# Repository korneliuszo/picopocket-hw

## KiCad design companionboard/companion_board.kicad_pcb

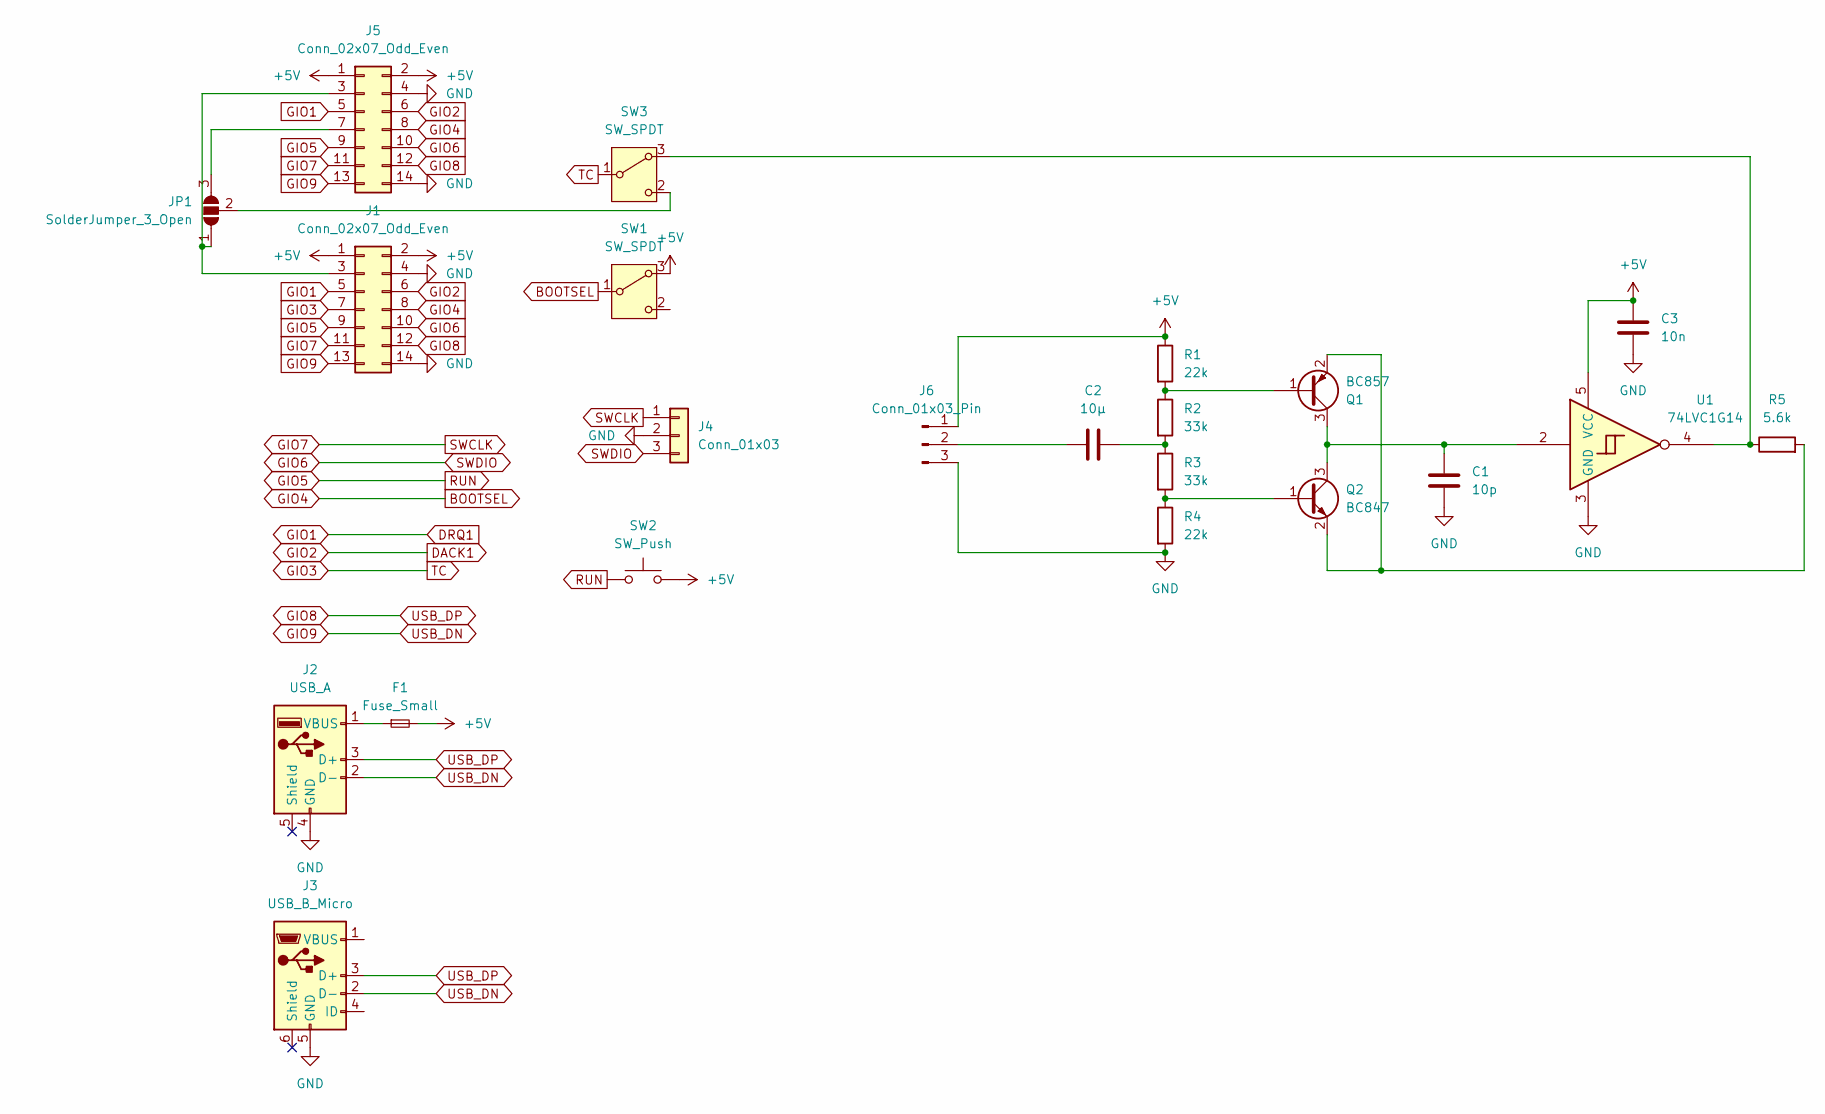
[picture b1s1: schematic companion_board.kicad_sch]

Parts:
C1: 10p; C_0805_2012Metric
C2: 10µ; C_0805_2012Metric
C3: 10n; C_0805_2012Metric
F1: Fuse_Small; Fuse_0805_2012Metric
J1: Conn_02x07_Odd_Even; EDGE-14
J2: USB_A; USB_A_CONNFLY_DS1095-WNR0
J3: USB_B_Micro; USB_Micro-B_Wuerth_614105150721_Vertical
J4: Conn_01x03; PinHeader_1x03_P2.54mm_Vertical
J5: Conn_02x07_Odd_Even; PinSocket_2x07_P2.00mm_Vertical
J6: Conn_01x03_Pin; PinHeader_1x03_P2.54mm_Vertical
JP1: SolderJumper_3_Open; SolderJumper-3_P2.0mm_Open_TrianglePad1.0x1.5mm
Q1: BC857; SOT-23
Q2: BC847; SOT-23
R1, R4: 22k; R_0402_1005Metric_Pad0.72x0.64mm_HandSolder
R2, R3: 33k; R_0402_1005Metric_Pad0.72x0.64mm_HandSolder
R5: 5.6k; R_0402_1005Metric_Pad0.72x0.64mm_HandSolder
SW1, SW3: SW_SPDT; SW_Slide-03_Wuerth-WS-SLTV_10x2.5x6.4_P2.54mm
SW2: SW_Push; SW_PUSH_6mm
U1: 74LVC1G14; SOT-353_SC-70-5_Handsoldering

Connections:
+5V: C3.1, F1.2, J1.1, J1.2, J5.1, J5.2, J6.1, R1.1, SW1.3 (A), SW2.2, U1.5 (VCC)
BOOTSEL: J1.8, J5.8, SW1.1 (B)
DACK1: J1.6, J5.6
DRQ1: J1.5, J5.5
GIO3: J1.7, SW3.1 (B)
GIO5: J1.9, J5.9, SW2.1
GIO6: J1.10, J4.3, J5.10
GIO7: J1.11, J4.1, J5.11
GIO8: J1.12, J2.3 (D+), J3.3 (D+), J5.12
GIO9: J1.13, J2.2 (D-), J3.2 (D-), J5.13
GND: C1.2, C3.2, J1.4, J1.14, J2.4 (GND), J3.5 (GND), J4.2, J5.4, J5.14, J6.3, R4.2, U1.3 (GND)
unnamed: C2.2, R2.2, R3.1
unnamed: J1.3, J5.3, JP1.1 (A)
unnamed: F1.1, J2.1 (VBUS)
unnamed: J5.7, JP1.3 (B)
unnamed: C2.1, J6.2
unnamed: JP1.2 (C), SW3.2 (C)
unnamed: Q1.1 (B), R1.2, R2.1
unnamed: C1.1, Q1.3 (C), Q2.3 (C), U1.2
unnamed: Q1.2 (E), Q2.2 (E), R5.2
unnamed: Q2.1 (B), R3.2, R4.1
unnamed: R5.1, SW3.3 (A), U1.4

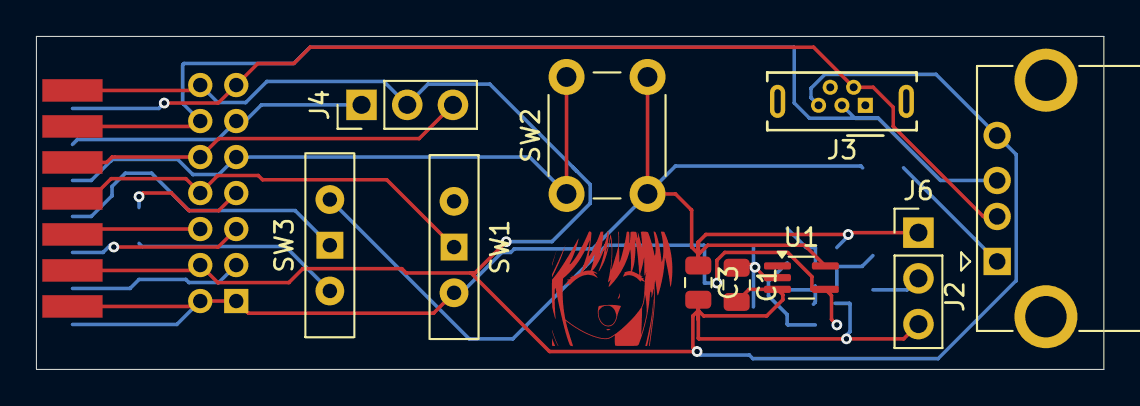
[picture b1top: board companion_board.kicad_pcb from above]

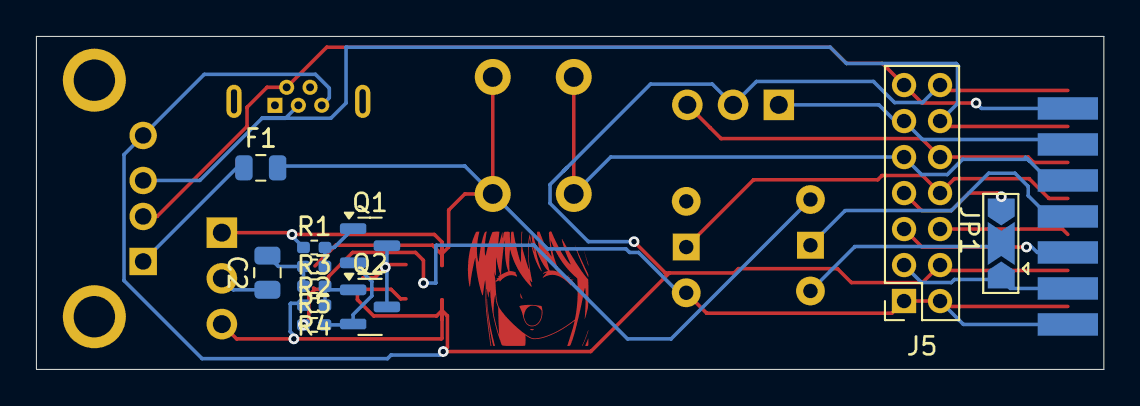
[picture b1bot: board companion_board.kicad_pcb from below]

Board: 2 copper layers, 59.3 x 18.5 mm, 22 parts (12 on the bottom side), 22 nets.

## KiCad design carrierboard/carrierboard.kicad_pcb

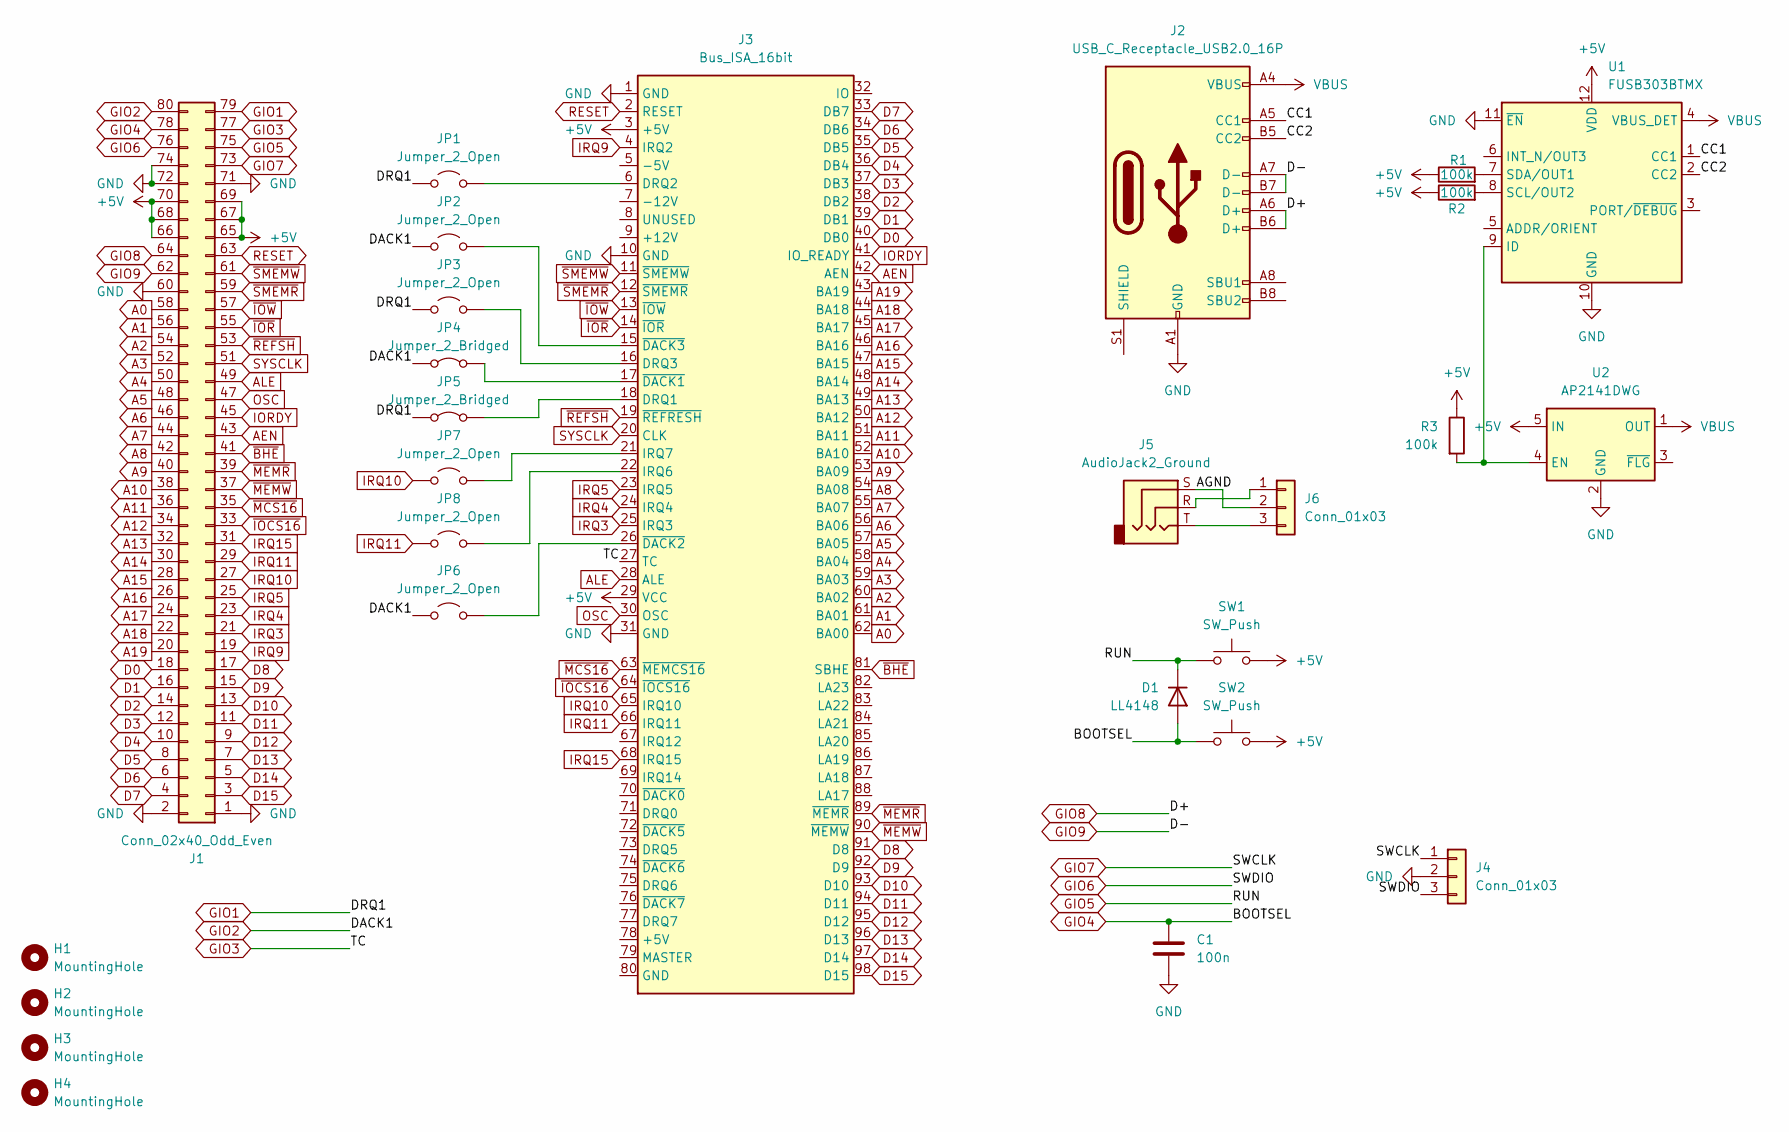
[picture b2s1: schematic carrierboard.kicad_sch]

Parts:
C1: 100n; C_0805_2012Metric
D1: LL4148; D_MiniMELF
H1, H2, H3, H4: MountingHole; MountingHole_2.7mm_M2.5_ISO14580_Pad
J1: Conn_02x40_Odd_Even
J2: USB_C_Receptacle_USB2.0_16P; USB_C_Receptacle_G-Switch_GT-USB-7010ASV
J3: Bus_ISA_16bit; BUS_AT
J4: Conn_01x03; PinHeader_1x03_P2.54mm_Vertical
J5: AudioJack2_Ground; Jack_3.5mm_CUI_SJ1-3523N_Horizontal
J6: Conn_01x03; Molex_PicoBlade_53261-0371_1x03-1MP_P1.25mm_Horizontal
JP1, JP2, JP3, JP6: Jumper_2_Open; PinHeader_2x01_P2.54mm_Vertical
JP4, JP5: Jumper_2_Bridged; PinHeader_2x01_P2.54mm_Vertical
JP7, JP8: Jumper_2_Open; SolderJumper-2_P1.3mm_Open_TrianglePad1.0x1.5mm
R1, R2, R3: 100k; R_0402_1005Metric
SW1, SW2: SW_Push; SW_Tactile_SKHH_Angled
U1: FUSB303BTMX; Texas_X2QFN-12_1.6x1.6mm_P0.4mm
U2: AP2141DWG; SOT-23-5

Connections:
+5V: J1.65, J1.66, J1.67, J1.68, J1.69, J1.70, J3.3 (+5V), J3.29 (VCC), R1.1, R2.1, R3.1, SW1.2, SW2.2, U1.12 (VDD), U2.5 (IN)
/AGND: J5.S, J6.2
/CC1: J2.A5 (CC1), U1.1 (CC1)
/CC2: J2.B5 (CC2), U1.2 (CC2)
A0: J1.58, J3.62 (BA00)
A1: J1.56, J3.61 (BA01)
A2: J1.54, J3.60 (BA02)
A3: J1.52, J3.59 (BA03)
A4: J1.50, J3.58 (BA04)
A5: J1.48, J3.57 (BA05)
A6: J1.46, J3.56 (BA06)
A7: J1.44, J3.55 (BA07)
A8: J1.42, J3.54 (BA08)
A9: J1.40, J3.53 (BA09)
A10: J1.38, J3.52 (BA10)
A11: J1.36, J3.51 (BA11)
A12: J1.34, J3.50 (BA12)
A13: J1.32, J3.49 (BA13)
A14: J1.30, J3.48 (BA14)
A15: J1.28, J3.47 (BA15)
A16: J1.26, J3.46 (BA16)
A17: J1.24, J3.45 (BA17)
A18: J1.22, J3.44 (BA18)
A19: J1.20, J3.43 (BA19)
AEN: J1.43, J3.42 (AEN)
ALE: J1.49, J3.28 (ALE)
D0: J1.18, J3.40 (DB0)
D1: J1.16, J3.39 (DB1)
D2: J1.14, J3.38 (DB2)
D3: J1.12, J3.37 (DB3)
D4: J1.10, J3.36 (DB4)
D5: J1.8, J3.35 (DB5)
D6: J1.6, J3.34 (DB6)
D7: J1.4, J3.33 (DB7)
D8: J1.17, J3.91 (D8)
D9: J1.15, J3.92 (D9)
D10: J1.13, J3.93 (D10)
D11: J1.11, J3.94 (D11)
D12: J1.9, J3.95 (D12)
D13: J1.7, J3.96 (D13)
D14: J1.5, J3.97 (D14)
D15: J1.3, J3.98 (D15)
GIO1: J1.79, JP1.1 (A), JP3.2 (B), JP5.1 (A)
GIO2: J1.80, JP2.1 (A), JP4.1 (A), JP6.1 (A)
GIO3: J1.77, J3.27 (TC)
GIO4: C1.1, D1.2 (A), J1.78, SW2.1
GIO5: D1.1 (K), J1.75, SW1.1
GIO6: J1.76, J4.3
GIO7: J1.73, J4.1
GIO8: J1.64, J2.A6 (D+), J2.B6 (D+)
GIO9: J1.62, J2.A7 (D-), J2.B7 (D-)
GND: C1.2, J1.1, J1.2, J1.60, J1.71, J1.72, J1.74, J2.A1 (GND), J2.A12 (GND), J2.B1 (GND), J2.B12 (GND), J3.1 (GND), J3.10 (GND), J3.31 (GND), J4.2, U1.10 (GND), U1.11 (~EN), U2.2 (GND)
IORDY: J1.45, J3.41 (IO_READY)
IRQ3: J1.21, J3.25 (IRQ3)
IRQ4: J1.23, J3.24 (IRQ4)
IRQ5: J1.25, J3.23 (IRQ5)
IRQ9: J1.19, J3.4 (IRQ2)
IRQ10: J1.27, J3.65 (IRQ10), JP7.1 (A)
IRQ11: J1.29, J3.66 (IRQ11), JP8.1 (A)
IRQ15: J1.31, J3.68 (IRQ15)
unnamed: J3.18 (DRQ1), JP5.2 (B)
unnamed: J3.6 (DRQ2), JP1.2 (B)
unnamed: J3.16 (DRQ3), JP3.1 (A)
unnamed: J3.22 (IRQ6), JP8.2 (B)
unnamed: J3.21 (IRQ7), JP7.2 (B)
unnamed: J3.17 (~DACK1), JP4.2 (B)
unnamed: J3.26 (~DACK2), JP6.2 (B)
unnamed: J3.15 (~DACK3), JP2.2 (B)
unnamed: J5.R, J6.1
unnamed: J5.T, J6.3
unnamed: R3.2, U1.9 (ID), U2.4 (EN)
unnamed: R2.2, U1.8 (SCL/OUT2)
unnamed: R1.2, U1.7 (SDA/OUT1)
OSC: J1.47, J3.30 (OSC)
RESET: J1.63, J3.2 (RESET)
SYSCLK: J1.51, J3.20 (CLK)
VBUS: J2.A4 (VBUS), J2.A9 (VBUS), J2.B4 (VBUS), J2.B9 (VBUS), U1.4 (VBUS_DET), U2.1 (OUT)
~BHE: J1.41, J3.81 (SBHE)
~IOCS16: J1.33, J3.64 (~IOCS16)
~IOR: J1.55, J3.14 (~IOR)
~IOW: J1.57, J3.13 (~IOW)
~MCS16: J1.35, J3.63 (~MEMCS16)
~MEMR: J1.39, J3.89 (~MEMR)
~MEMW: J1.37, J3.90 (~MEMW)
~REFSH: J1.53, J3.19 (~REFRESH)
~SMEMR: J1.59, J3.12 (~SMEMR)
~SMEMW: J1.61, J3.11 (~SMEMW)

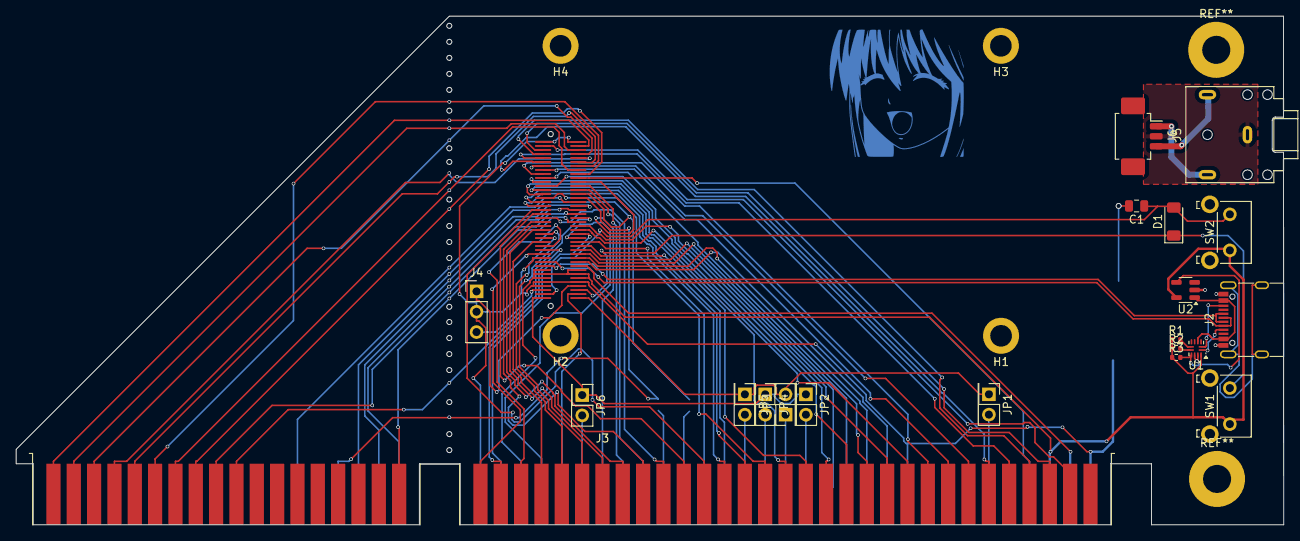
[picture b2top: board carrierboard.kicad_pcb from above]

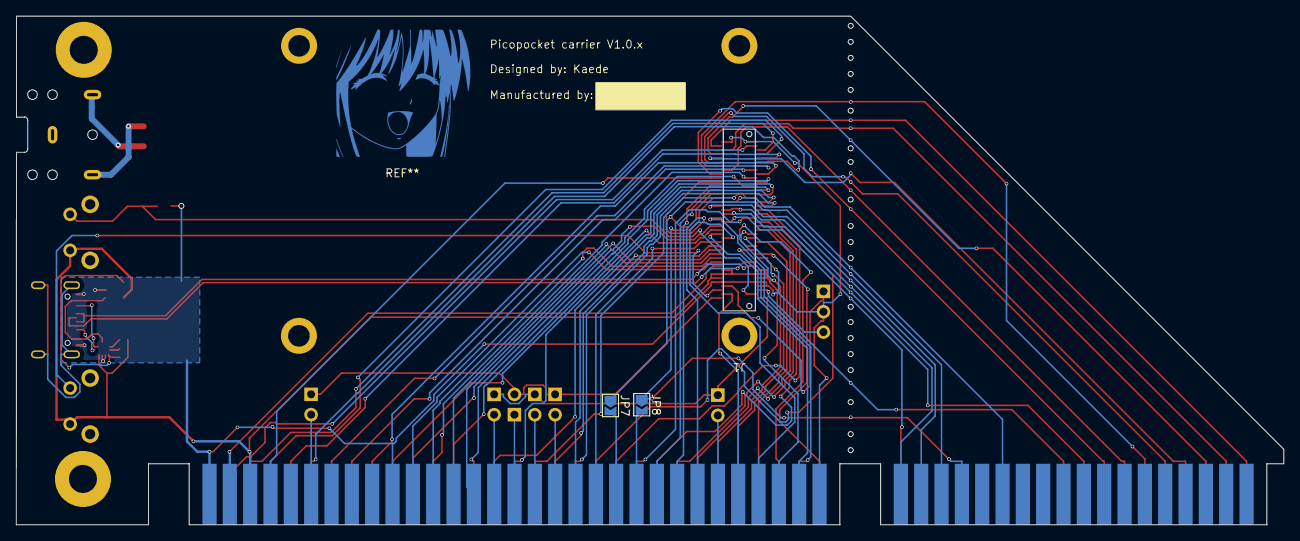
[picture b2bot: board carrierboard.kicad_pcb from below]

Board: 2 copper layers, 158.3 x 63.5 mm, 27 parts (3 on the bottom side), 87 nets.

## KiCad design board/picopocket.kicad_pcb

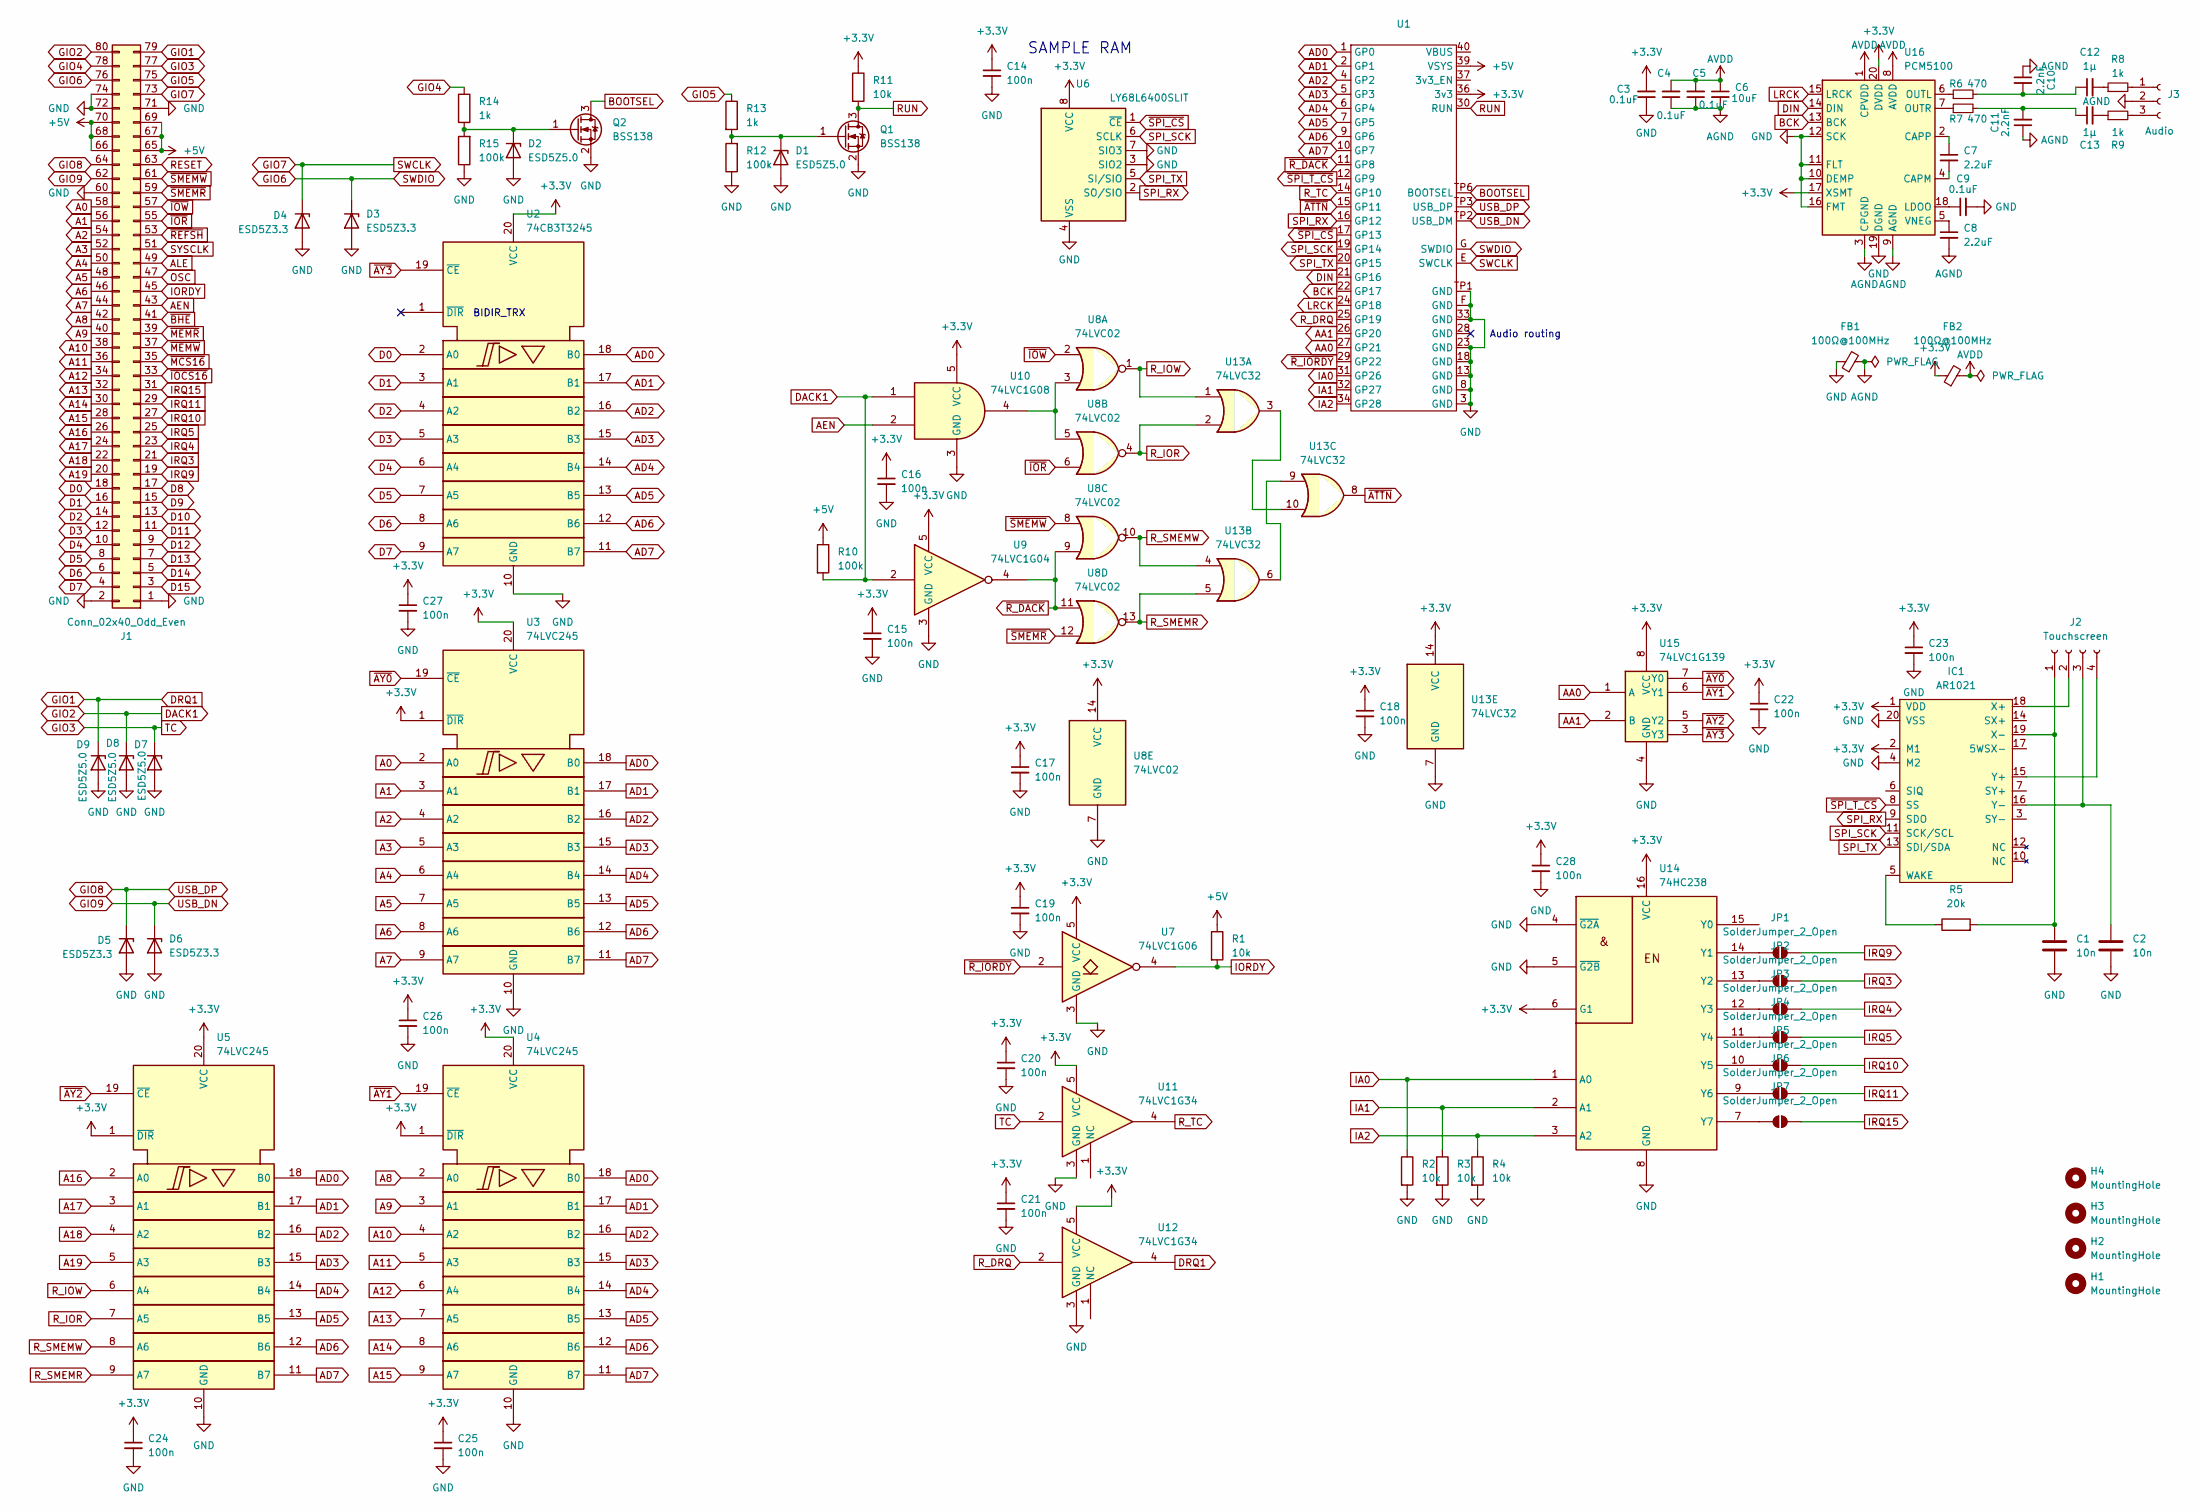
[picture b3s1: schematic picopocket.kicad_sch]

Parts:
C1, C2: 10n; C_0603_1608Metric; MPN C376807
C3, C4, C5, C9: 0.1uF; C_0402_1005Metric; MPN C361203
C6: 10uF; C_0805_2012Metric; MPN C1713
C7, C8: 2.2uF; C_0402_1005Metric; MPN C385032
C10, C11: 2.2nF; C_0603_1608Metric; MPN C107082
C12, C13: 1µ; C_1206_3216Metric; MPN C444884
C14, C15, C16, C17, C18, C19, C20, C21, C22, C23, C24, C25, C26, C27, C28: 100n; C_0201_0603Metric; MPN C5142565
D1, D2, D7, D8, D9: ESD5Z5.0; D_SOD-523; MPN C475685
D3, D4, D5, D6: ESD5Z3.3; D_SOD-523; MPN C475684
FB1, FB2: 100Ω@100MHz; L_0805_2012Metric; MPN C124102
H1, H2, H3, H4: MountingHole; MountingHole_2.7mm_M2.5_ISO14580_Pad
IC1: AR1021; SSOP-20_5.3x7.2mm_P0.65mm; MPN C220291; Farnell 2218568
J1: Conn_02x40_Odd_Even; XKB Male 80P 0.5P
J2: Touchscreen; Molex_PicoBlade_53261-0471_1x04-1MP_P1.25mm_Horizontal
J3: Audio; Molex_PicoBlade_53261-0371_1x03-1MP_P1.25mm_Horizontal
JP1, JP2, JP3, JP4, JP5, JP6, JP7: SolderJumper_2_Open; SolderJumper-2_P1.3mm_Open_TrianglePad1.0x1.5mm
Q1, Q2: BSS138; SOT-23; MPN C5337205
R1, R2, R3, R4, R11: 10k; R_0402_1005Metric; MPN C163811
R5: 20k; R_0402_1005Metric; MPN C3017501
R6, R7: 470; R_0402_1005Metric; MPN C3015779
R8, R9, R13, R14: 1k; R_0402_1005Metric; MPN C3152105
R10, R12, R15: 100k; R_0402_1005Metric; MPN C176119
U1: MODULE_SC0918
U2: 74CB3T3245; TSSOP-20_4.4x6.5mm_P0.65mm; MPN C1547227
U3, U4, U5: 74LVC245; TSSOP-20_4.4x6.5mm_P0.65mm; MPN C6082
U6: LY68L6400SLIT; SOIC-8_3.9x4.9mm_P1.27mm; MPN C261881
U7: 74LVC1G06; SOT-23-5; MPN C840103
U8: 74LVC02; TSSOP-14_4.4x5mm_P0.65mm; MPN C75069
U9: 74LVC1G04; SOT-23-5; MPN C460517
U10: 74LVC1G08; SOT-23-5; MPN C434068
U11, U12: 74LVC1G34; SOT-23-5; MPN C840096
U13: 74LVC32; TSSOP-14_4.4x5mm_P0.65mm; MPN C352974
U14: 74HC238; TSSOP-16_4.4x5mm_P0.65mm; MPN C60434
U15: 74LVC1G139; VSSOP-8_2.4x2.1mm_P0.5mm; MPN C153798
U16: PCM5100; TSSOP-20_4.4x6.5mm_P0.65mm; MPN C131154

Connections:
+3.3V: C3.2, C14.1, C15.1, C16.1, C17.1, C18.1, C19.1, C20.1, C21.1, C22.1, C23.1, C24.1, C25.1, C26.1, C27.1, C28.1, FB2.1, IC1.1 (VDD), IC1.2 (M1), R11.1, U1.36 (3v3), U2.20 (VCC), U3.1 (~DIR), U3.20 (VCC), U4.1 (~DIR), U4.20 (VCC), U5.1 (~DIR), U5.20 (VCC), U6.8 (VCC), U7.5 (VCC), U8.14 (VCC), U9.5 (VCC), U10.5 (VCC), U11.5 (VCC), U12.5 (VCC), U13.14 (VCC), U14.6 (G1), U14.16 (VCC), U15.8 (VCC), U16.17 (XSMT), U16.20 (DVDD)
+5V: J1.65, J1.66, J1.67, J1.68, J1.69, J1.70, R1.1, R10.1, U1.39 (VSYS)
A0: J1.58, U3.2 (A0)
A1: J1.56, U3.3 (A1)
A2: J1.54, U3.4 (A2)
A3: J1.52, U3.5 (A3)
A4: J1.50, U3.6 (A4)
A5: J1.48, U3.7 (A5)
A6: J1.46, U3.8 (A6)
A7: J1.44, U3.9 (A7)
A8: J1.42, U4.2 (A0)
A9: J1.40, U4.3 (A1)
A10: J1.38, U4.4 (A2)
A11: J1.36, U4.5 (A3)
A12: J1.34, U4.6 (A4)
A13: J1.32, U4.7 (A5)
A14: J1.30, U4.8 (A6)
A15: J1.28, U4.9 (A7)
A16: J1.26, U5.2 (A0)
A17: J1.24, U5.3 (A1)
A18: J1.22, U5.4 (A2)
A19: J1.20, U5.5 (A3)
AA0: U1.27 (GP21), U15.1 (A)
AA1: U1.26 (GP20), U15.2 (B)
AD0: U1.1 (GP0), U2.18 (B0), U3.18 (B0), U4.18 (B0), U5.18 (B0)
AD1: U1.2 (GP1), U2.17 (B1), U3.17 (B1), U4.17 (B1), U5.17 (B1)
AD2: U1.4 (GP2), U2.16 (B2), U3.16 (B2), U4.16 (B2), U5.16 (B2)
AD3: U1.5 (GP3), U2.15 (B3), U3.15 (B3), U4.15 (B3), U5.15 (B3)
AD4: U1.6 (GP4), U2.14 (B4), U3.14 (B4), U4.14 (B4), U5.14 (B4)
AD5: U1.7 (GP5), U2.13 (B5), U3.13 (B5), U4.13 (B5), U5.13 (B5)
AD6: U1.9 (GP6), U2.12 (B6), U3.12 (B6), U4.12 (B6), U5.12 (B6)
AD7: U1.10 (GP7), U2.11 (B7), U3.11 (B7), U4.11 (B7), U5.11 (B7)
AEN: J1.43, U10.2
AGND: C4.1, C5.1, C6.2, C8.2, C10.1, C11.1, FB1.2, J3.2, U16.3 (CPGND), U16.9 (AGND)
ALE: J1.49
AVDD: C4.2, C5.2, C6.1, FB2.2, U16.1 (CPVDD), U16.8 (AVDD)
BCK: U1.22 (GP17), U16.13 (BCK)
BOOTSEL: Q2.3 (D), U1.TP6 (BOOTSEL)
D0: J1.18, U2.2 (A0)
D1: J1.16, U2.3 (A1)
D2: J1.14, U2.4 (A2)
D3: J1.12, U2.5 (A3)
D4: J1.10, U2.6 (A4)
D5: J1.8, U2.7 (A5)
D6: J1.6, U2.8 (A6)
D7: J1.4, U2.9 (A7)
D8: J1.17
D9: J1.15
D10: J1.13
D11: J1.11
D12: J1.9
D13: J1.7
D14: J1.5
D15: J1.3
DACK1: D8.1 (K), J1.80, R10.2, U9.2, U10.1
DIN: U1.21 (GP16), U16.14 (DIN)
DRQ1: D9.1 (K), J1.79, U12.4
GIO3: D7.1 (K), J1.77, U11.2
GIO4: J1.78, R14.1
GIO5: J1.75, R13.1
GIO6: D3.1 (K), J1.76, U1.G (SWDIO)
GIO7: D4.1 (K), J1.73, U1.E (SWCLK)
GIO8: D5.1 (K), J1.64, U1.TP3 (USB_DP)
GIO9: D6.1 (K), J1.62, U1.TP2 (USB_DM)
GND: C1.2, C2.2, C3.1, C9.2, C14.2, C15.2, C16.2, C17.2, C18.2, C19.2, C20.2, C21.2, C22.2, C23.2, C24.2, C25.2, C26.2, C27.2, C28.2, D1.2 (A), D2.2 (A), D3.2 (A), D4.2 (A), D5.2 (A), D6.2 (A), D7.2 (A), D8.2 (A), D9.2 (A), FB1.1, IC1.4 (M2), IC1.20 (VSS), J1.1, J1.2, J1.60, J1.71, J1.72, J1.74, Q1.2 (S), Q2.2 (S), R2.2, R3.2, R4.2, R12.1, R15.1, U1.3 (GND), U1.8 (GND), U1.13 (GND), U1.18 (GND), U1.23 (GND), U1.33 (GND), U1.F (GND), U1.TP1 (GND), U2.10 (GND), U3.10 (GND), U4.10 (GND), U5.10 (GND), U6.3 (SIO2), U6.4 (VSS), U6.7 (SIO3), U7.3 (GND), U8.7 (GND), U9.3 (GND), U10.3 (GND), U11.3 (GND), U12.3 (GND), U13.7 (GND), U14.4 (~G2A), U14.5 (~G2B), U14.8 (GND), U15.4 (GND), U16.10 (DEMP), U16.11 (FLT), U16.12 (SCK), U16.16 (FMT), U16.19 (DGND)
IA0: R2.1, U1.31 (GP26), U14.1 (A0)
IA1: R3.1, U1.32 (GP27), U14.2 (A1)
IA2: R4.1, U1.34 (GP28), U14.3 (A2)
IORDY: J1.45, R1.2, U7.4
IRQ3: J1.21, JP2.2 (B)
IRQ4: J1.23, JP3.2 (B)
IRQ5: J1.25, JP4.2 (B)
IRQ9: J1.19, JP1.2 (B)
IRQ10: J1.27, JP5.2 (B)
IRQ11: J1.29, JP6.2 (B)
IRQ15: J1.31, JP7.2 (B)
LRCK: U1.24 (GP18), U16.15 (LRCK)
unnamed: C10.2, C12.1, R6.2
unnamed: C11.2, C13.1, R7.2
unnamed: C12.2, R8.1
unnamed: C13.2, R9.1
unnamed: D1.1 (K), Q1.1 (G), R12.2, R13.2
unnamed: D2.1 (K), Q2.1 (G), R14.2, R15.2
unnamed: IC1.5 (WAKE), R5.1
unnamed: IC1.18 (X+), J2.2
unnamed: C1.1, IC1.19 (X-), J2.1, R5.2
unnamed: IC1.15 (Y+), J2.4
unnamed: C2.1, IC1.16 (Y-), J2.3
unnamed: J3.1, R8.2
unnamed: J3.3, R9.2
unnamed: JP1.1 (A), U14.14 (Y1)
unnamed: JP2.1 (A), U14.13 (Y2)
unnamed: JP3.1 (A), U14.12 (Y3)
unnamed: JP4.1 (A), U14.11 (Y4)
unnamed: JP5.1 (A), U14.10 (Y5)
unnamed: JP6.1 (A), U14.9 (Y6)
unnamed: JP7.1 (A), U14.7 (Y7)
unnamed: U8.3, U8.5, U10.4
unnamed: U13.6, U13.9
unnamed: U13.3, U13.10
unnamed: C7.2, U16.4 (CAPM)
unnamed: C7.1, U16.2 (CAPP)
unnamed: C9.1, U16.18 (LDOO)
unnamed: R6.1, U16.6 (OUTL)
unnamed: R7.1, U16.7 (OUTR)
unnamed: C8.1, U16.5 (VNEG)
OSC: J1.47
RESET: J1.63
RUN: Q1.3 (D), R11.2, U1.30 (RUN)
R_DRQ: U1.25 (GP19), U12.2
R_IOR: U5.7 (A5), U8.4, U13.2
R_IOW: U5.6 (A4), U8.1, U13.1
R_SMEMR: U5.9 (A7), U8.13, U13.5
R_SMEMW: U5.8 (A6), U8.10, U13.4
R_TC: U1.14 (GP10), U11.4
SPI_RX: IC1.9 (SDO), U1.16 (GP12), U6.2 (SO/SIO)
SPI_SCK: IC1.11 (SCK/SCL), U1.19 (GP14), U6.6 (SCLK)
SPI_TX: IC1.13 (SDI/SDA), U1.20 (GP15), U6.5 (SI/SIO)
SYSCLK: J1.51
~ATTN: U1.15 (GP11), U13.8
~AY0: U3.19 (~CE), U15.7 (Y0)
~AY1: U4.19 (~CE), U15.6 (Y1)
~AY2: U5.19 (~CE), U15.5 (Y2)
~AY3: U2.19 (~CE), U15.3 (Y3)
~BHE: J1.41
~IOCS16: J1.33
~IOR: J1.55, U8.6
~IOW: J1.57, U8.2
~MCS16: J1.35
~MEMR: J1.39
~MEMW: J1.37
~REFSH: J1.53
~R_DACK: U1.11 (GP8), U8.9, U8.11, U9.4
~R_IORDY: U1.29 (GP22), U7.2
~SMEMR: J1.59, U8.12
~SMEMW: J1.61, U8.8
~SPI_CS: U1.17 (GP13), U6.1 (~CE)
~SPI_T_CS: IC1.8 (SS), U1.12 (GP9)

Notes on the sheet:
Audio routing
SAMPLE RAM
BIDIR_TRX

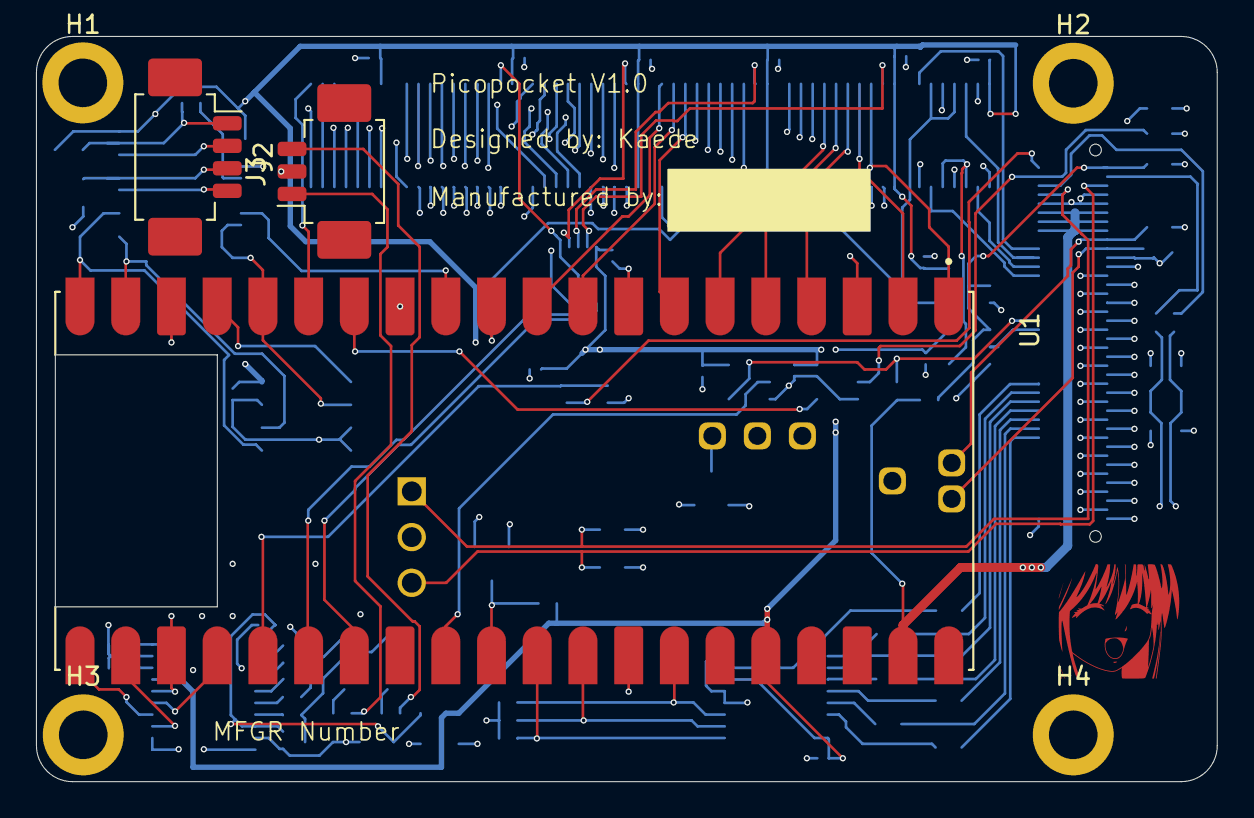
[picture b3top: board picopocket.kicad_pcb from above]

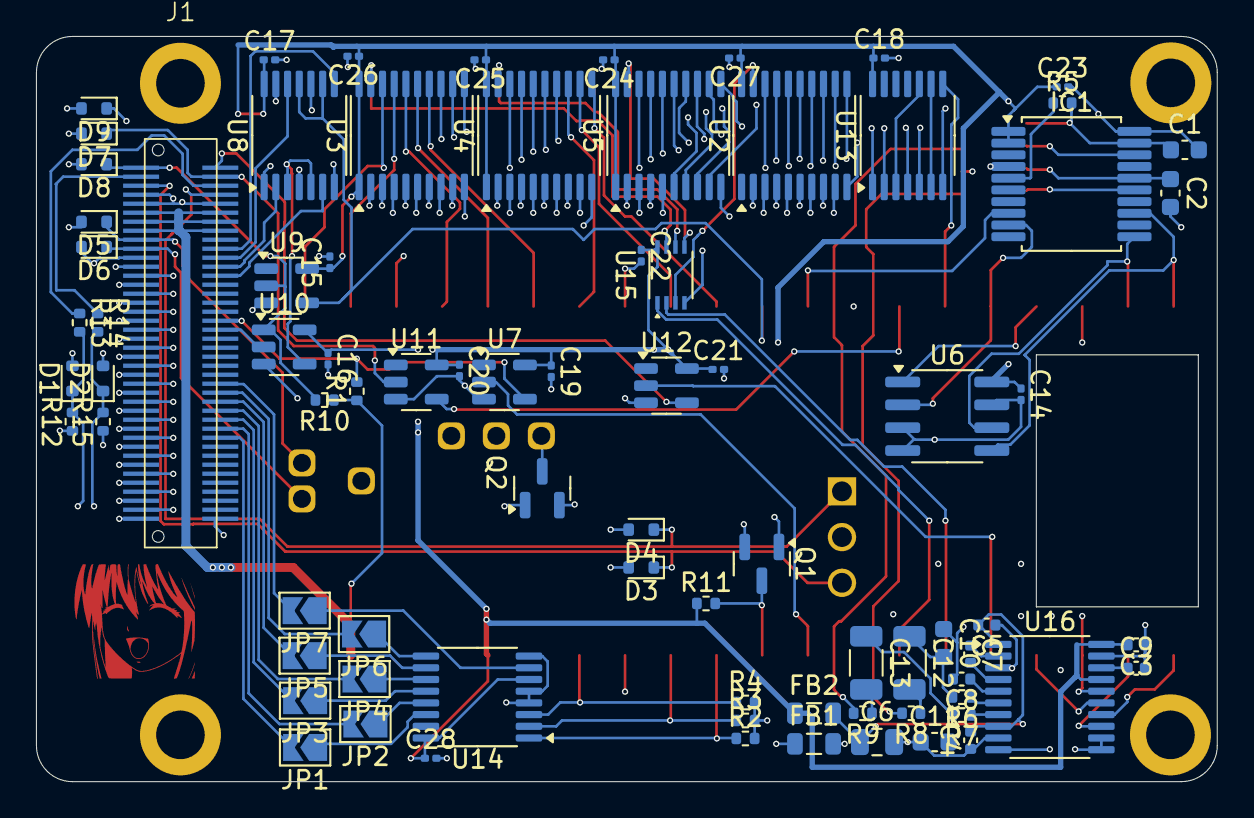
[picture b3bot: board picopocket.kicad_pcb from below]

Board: 4 copper layers, 65.6 x 41.4 mm, 87 parts (80 on the bottom side), 120 nets.

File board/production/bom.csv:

Designator,Footprint,Quantity,Value,LCSC Part #
"C1, C2",0603,2,10n,C376807
"C10, C11",0603,2,2.2nF,C107082
"C12, C13",1206,2,1µ,C444884
"C14, C15, C16, C17, C18, C19, C20, C21, C22, C23, C24, C25, C26, C27, C28",0201,15,100n,C5142565
"C3, C4, C5, C9",0402,4,0.1uF,C361203
C6,0805,1,10uF,C1713
"C7, C8",0402,2,2.2uF,C385032
"D1, D2, D7, D8, D9",D_SOD-523,5,ESD5Z5.0,C475685
"D3, D4, D5, D6",D_SOD-523,4,ESD5Z3.3,C475684
"FB1, FB2",0805,2,100Ω@100MHz,C124102
IC1,SSOP-20_5.3x7.2mm_P0.65mm,1,AR1021,C220291
"Q1, Q2",SOT-23,2,BSS138,C5337205
"R1, R11, R2, R3, R4",0402,5,10k,C163811
"R10, R12, R15",0402,3,100k,C176119
"R13, R14, R8, R9",0402,4,1k,C3152105
R5,0402,1,20k,C3017501
"R6, R7",0402,2,470,C3015779
U10,SOT-23-5,1,74LVC1G08,C434068
"U11, U12",SOT-23-5,2,74LVC1G34,C840096
U13,TSSOP-14_4.4x5mm_P0.65mm,1,74LVC32,C352974
U14,TSSOP-16_4.4x5mm_P0.65mm,1,74HC238,C60434
U15,VSSOP-8_2.4x2.1mm_P0.5mm,1,74LVC1G139,C153798
U16,TSSOP-20_4.4x6.5mm_P0.65mm,1,PCM5100,C131154
U2,TSSOP-20_4.4x6.5mm_P0.65mm,1,74CB3T3245,C1547227
"U3, U4, U5",TSSOP-20_4.4x6.5mm_P0.65mm,3,74LVC245,C6082
U6,SOIC-8_3.9x4.9mm_P1.27mm,1,LY68L6400SLIT,C261881
U7,SOT-23-5,1,74LVC1G06,C840103
U8,TSSOP-14_4.4x5mm_P0.65mm,1,74LVC02,C75069
U9,SOT-23-5,1,74LVC1G04,C460517

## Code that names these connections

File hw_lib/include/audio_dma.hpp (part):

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    }
};

template <uint PIN_DIN,uint PIN_BCK,uint PIN_LRCK, uint PION, uint IRQN>
class AudioDMA_Impl {
	static_assert(PIN_BCK + 1 == PIN_LRCK);
public:
	static inline uint pio_sm;

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				pio,
				pio_sm,
				program_offset,
				PIN_DIN,
				PIN_BCK);
	    ping_dma_chan = dma_claim_unused_channel(true);
	    pong_dma_chan = dma_claim_unused_channel(true);
	    pio_sm_set_enabled(pio,pio_sm,1);
	    pio_gpio_init(pio, PIN_DIN);
	    pio_gpio_init(pio, PIN_BCK);
	    pio_gpio_init(pio, PIN_LRCK);
	}

	static void deinit()
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
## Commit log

2024-04-04 Version 1.0
2024-04-06 Fix AR1021 footprint
2024-04-06 Fix divets in connector
2024-04-06 Add companion board
2024-04-06 Change to 74HC238 (avalibility)
2024-04-06 Replace to correct mounting hole, reroute accordingly
2024-04-06 Lock layout
2024-04-06 Update footprint to match exactly one on serial card
    Thanks HeathenUK
2024-04-07 Add jlcpcb part numbers
2024-04-07 Add production files
2024-04-07 Add companion board production files
2024-04-07 Some random save
2024-05-13 MEM/IO access works
2024-05-13 Gitignorize
2024-05-13 Random project change
2024-05-13 PCLK/8 stable
2024-05-16 Add first test firmware
2024-05-19 Fix DMA implementation
2024-05-19 Add DMA tests
2024-05-21 Test irqs
2024-05-31 Add PSRAM test + scaffolding for touchscreen chip
2024-05-31 int already so use int
2024-05-31 PCLK/5
2024-06-03 Implement AR1021
2024-06-03 100-120ns
2024-06-10 Add audio playback (loud)
2024-06-10 make quieter by ~8bits
2024-06-10 Silence ... to be enabled back by revert
2024-06-10 Fixes in library
2024-06-10 Show digitizer on display
2024-06-10 Revert "Silence ... to be enabled back by revert"
    This reverts commit 0d2a703af32f2540bf7970c9cecbca40dd3fed44.
2024-06-13 fix .gitignore
2024-06-13 Move main board schematics around
2024-06-13 Add licence stuff
2024-07-16 Prepare for no driven reads
2024-07-16 Short spi code so spi for wifi fits
2024-07-22 Update to random develop commit as there is patch for CYW43_PIO_CLOCK_DIV
2024-07-28 Add support for PICO_PANIC_NO_STRINGS_ON_TARGET
2024-09-16 Carrierboard for comments
2024-09-16 Prepare next rev as published V1.0 has bugs
2024-09-16 Fix traces from group move
2024-10-21 Remove nontatomicity
2024-10-21 Optimize ISA PIO
2024-10-23 Fix DMA
2024-10-25 Slow down pico to 250MHz - still 16MHz ISA possible
2024-11-01 Add picopocket_sim target
2024-12-03 assumed stack alignment on x86 for vector instructions
2024-12-08 Remove constraint of add_device call
2024-12-10 Fix sim restarting
2024-12-12 Fix build
2024-12-15 Add way to do most code in flash
2024-12-22 Fix races in irq setting from 2 cores
2024-12-25 Allow providing other boards
2024-12-25 Fix FAKE_READ
2024-12-25 Provide stub AR1021 when not installed
2024-12-27 Fix PSRAM
2024-12-27 Allow disconnecting disconnected map
2024-12-30 Add needed functions to audio core
2024-12-30 Improvements in api
2024-12-31 make audio_dma 2 times includeable
2024-12-31 Add systick measurement of used cpu time
2025-01-02 Wait in IOCHRDY for pico initialization
2025-01-07 Flash was overclocked
2025-01-19 Update companionboard with line in input
2025-01-20 Tidy up board
2025-01-20 Update zip for production
2025-01-26 PSRAM dma high priority
2025-01-26 Fix compatibility with clear pocket
2025-01-26 Add tracer target
2025-02-15 proper default to picopocket board
2025-02-15 fix test firmware
2025-02-15 Seperate TC line usage
2025-02-15 Make audio clean pio instruction space
2025-02-17 Remove unneeded nop
2025-02-17 Add TX DMA helper functions
2025-02-17 Add forgotten things in deinit
2025-02-17 Add analog input
2025-02-18 Expose more things outside
2025-02-18 DMA_TX_ready_data function
2025-02-18 Fix flipped connector
2025-02-18 Production files
2025-04-14 pio_sm value is sometimes needed outside - spaghetti code
2025-04-15 New SDK

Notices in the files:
hw_lib/include/audio_dma.hpp:
SPDX-FileCopyrightText: Korneliusz Osmenda <korneliuszo@gmail.com>
SPDX-License-Identifier: MIT
